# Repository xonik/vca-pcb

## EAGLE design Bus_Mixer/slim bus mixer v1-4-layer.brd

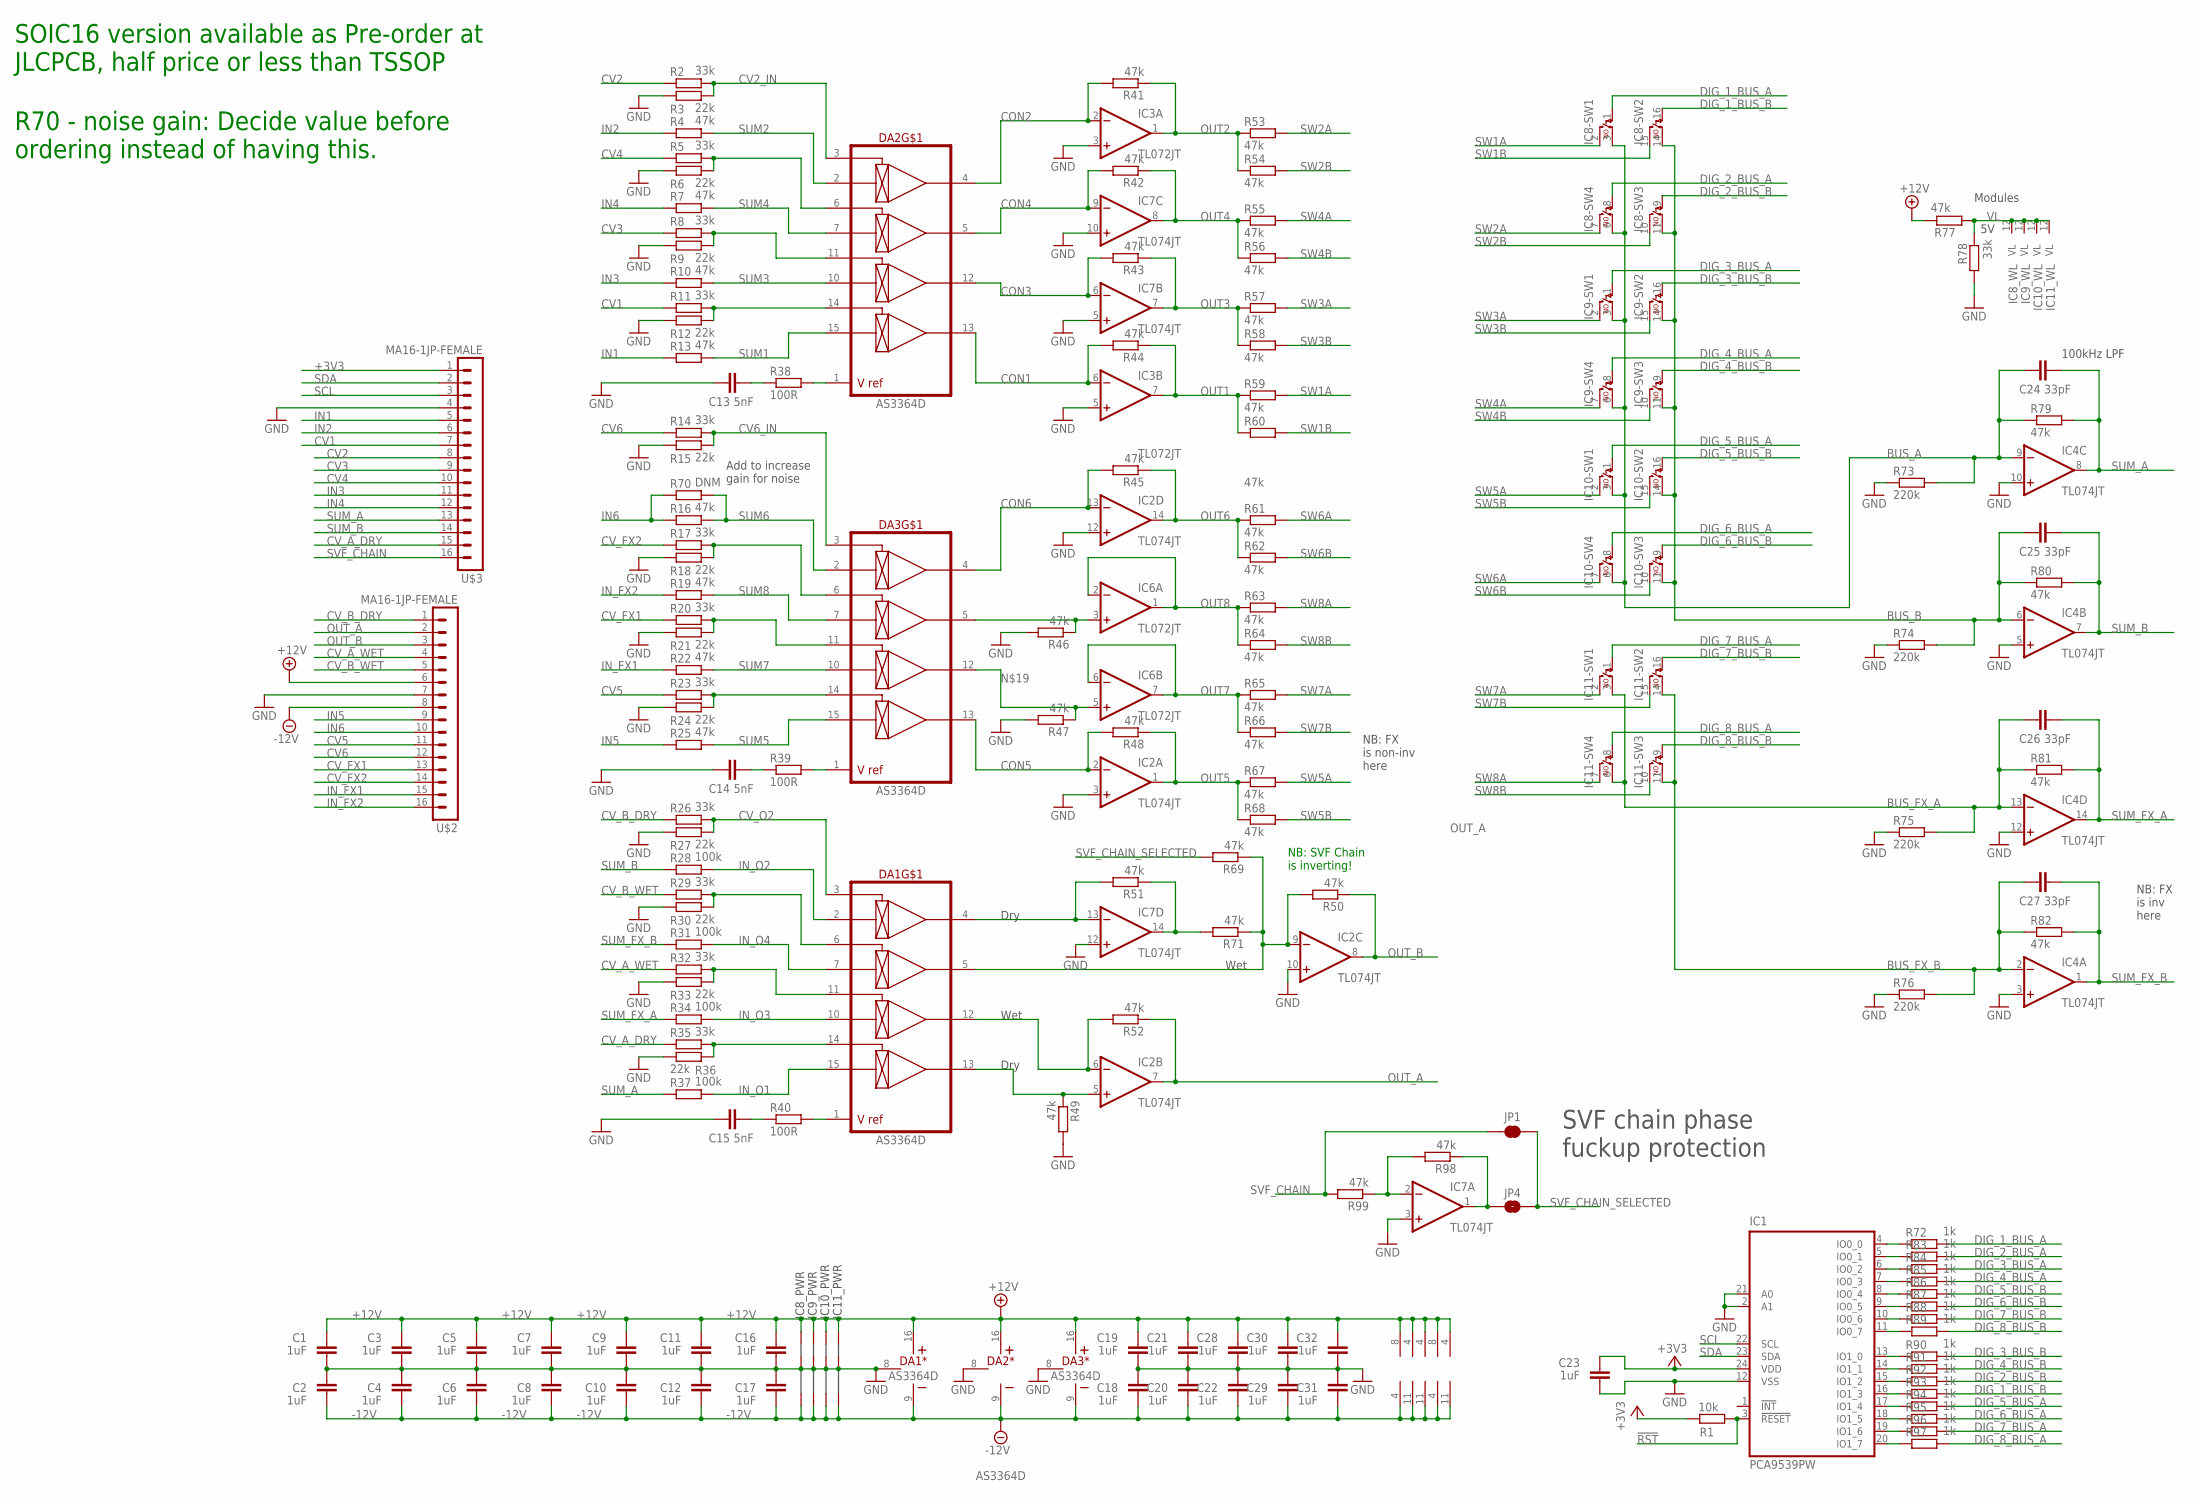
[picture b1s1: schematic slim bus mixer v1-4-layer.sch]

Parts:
C1, C2, C3, C4, C5, C6, C7, C8, C9, C10, C11, C12, C16, C17, C18, C19, C20, C21, C22, C23, C28, C29, C30, C31, C32: 1uF; C0402-J
C13, C14, C15: 5nF; C0402-J
C24, C25, C26, C27: 33pF; C0402-J
DA1, DA2, DA3: AS3364D; DIL16J
IC1: PCA9539PW; TSSOP24J
IC2, IC4, IC7: TL074JT; TSSOP14J
IC3, IC6: TL072JT; TSSOP8J
IC8, IC9, IC10, IC11: DG412-JS; SO-16
JP1: JUMPER-SMT_2_NC_TRACE_SILK-DNM; SMT-JUMPER_2_NC_TRACE_SILK
JP4: JUMPER-SMT_2_NO_SILK-DNM; SMT-JUMPER_2_NO_SILK
R1: 10k; R0402
R2, R5, R8, R11, R14, R17, R20, R23, R26, R29, R32, R35, R78: 33k; R0402
R3, R6, R9, R12, R15, R18, R21, R24, R27, R30, R33, R36: 22k; R0402
R4, R7, R10, R13, R16, R19, R22, R25, R41, R42, R43, R44, R45, R46, R47, R48, R49, R50, R51, R52, R53, R54, R55, R56, R57, R58, R59, R60, R61, R62, R63, R64, R65, R66, R67, R68, R69, R71, R77, R79, R80, R81, R82, R98, R99: 47k; R0402
R28, R31, R34, R37: 100k; R0402
R38, R39, R40: 100R; R0402
R70: DNM; R0805
R72, R83, R84, R85, R86, R87, R88, R89, R90, R91, R92, R93, R94, R95, R96, R97: 1k; R0402
R73, R74, R75, R76: 220k; R0603
U$2, U$3: MA16-1JP-FEMALE; SIP-PIN16-1J

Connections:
!RST: IC1.3 (!RESET), R1.2
+3V3: C23.2, IC1.24 (VDD), R1.1, U$3.1
+12V: C1.2, C3.2, C5.2, C7.2, C9.2, C11.2, C16.2, C19.2, C21.2, C28.2, C30.2, C32.2, DA1.16 (V+), DA2.16 (V+), DA3.16 (V+), IC2.4 (V+), IC3.8 (V+), IC4.4 (V+), IC6.8 (V+), IC7.4 (V+), IC8.13 (+15V), IC9.13 (+15V), IC10.13 (+15V), IC11.13 (+15V), R77.1, U$2.6
-12V: C2.1, C4.1, C6.1, C8.1, C10.1, C12.1, C17.1, C18.1, C20.1, C22.1, C29.1, C31.1, DA1.9 (V-), DA2.9 (V-), DA3.9 (V-), IC2.11 (V-), IC3.4 (V-), IC4.11 (V-), IC6.4 (V-), IC7.11 (V-), IC8.4 (-15V), IC9.4 (-15V), IC10.4 (-15V), IC11.4 (-15V), U$2.8
BUS_A: C24.1, IC4.9 (-IN), IC8.3 (S), IC8.6 (S), IC9.3 (S), IC9.6 (S), IC10.3 (S), IC10.6 (S), R73.2, R79.1
BUS_B: C25.1, IC4.6 (-IN), IC8.11 (S), IC8.14 (S), IC9.11 (S), IC9.14 (S), IC10.11 (S), IC10.14 (S), R74.2, R80.1
BUS_FX_A: C26.1, IC4.13 (-IN), IC11.3 (S), IC11.6 (S), R75.2, R81.1
BUS_FX_B: C27.1, IC4.2 (-IN), IC11.11 (S), IC11.14 (S), R76.2, R82.1
CON1: DA2.13 (OUT4), IC3.6 (-IN), R44.2
CON2: DA2.4 (OUT1), IC3.2 (-IN), R41.2
CON3: DA2.12 (OUT3), IC7.6 (-IN), R43.2
CON4: DA2.5 (OUT2), IC7.9 (-IN), R42.2
CON5: DA3.13 (OUT4), IC2.2 (-IN), R48.2
CON6: DA3.4 (OUT1), IC2.13 (-IN), R45.2
CON_O1: DA1.12 (OUT3), IC2.6 (-IN), R52.2
CV1: R11.1, U$3.7
CV2: R2.1, U$3.8
CV2_IN: DA2.3 (CV1), R2.2, R3.2
CV3: R8.1, U$3.9
CV4: R5.1, U$3.10
CV5: R23.1, U$2.11
CV6: R14.1, U$2.12
CV6_IN: DA3.3 (CV1), R14.2, R15.2
CV_A_DRY: R35.1, U$3.15
CV_A_WET: R32.1, U$2.4
CV_B_DRY: R26.1, U$2.1
CV_B_WET: R29.1, U$2.5
CV_FX1: R20.1, U$2.13
CV_FX2: R17.1, U$2.14
CV_O2: DA1.3 (CV1), R26.2, R27.2
DIG_1_BUS_A: IC8.1 (C), R72.2
DIG_1_BUS_B: IC8.16 (C), R93.2
DIG_2_BUS_A: IC8.8 (C), R83.2
DIG_2_BUS_B: IC8.9 (C), R92.2
DIG_3_BUS_A: IC9.1 (C), R84.2
DIG_3_BUS_B: IC9.16 (C), R90.2
DIG_4_BUS_A: IC9.8 (C), R85.2
DIG_4_BUS_B: IC9.9 (C), R91.2
DIG_5_BUS_A: IC10.1 (C), R94.2
DIG_5_BUS_B: IC10.16 (C), R86.2
DIG_6_BUS_A: IC10.8 (C), R95.2
DIG_6_BUS_B: IC10.9 (C), R87.2
DIG_7_BUS_A: IC11.1 (C), R96.2
DIG_7_BUS_B: IC11.16 (C), R88.2
DIG_8_BUS_A: IC11.8 (C), R97.2
DIG_8_BUS_B: IC11.9 (C), R89.2
GND: C1.1, C2.2, C3.1, C4.2, C5.1, C6.2, C7.1, C8.2, C9.1, C10.2, C11.1, C12.2, C13.1, C14.1, C15.1, C16.1, C17.2, C18.2, C19.1, C20.2, C21.1, C22.2, C23.1, C28.1, C29.2, C30.1, C31.2, C32.1, DA1.8 (GND), DA2.8 (GND), DA3.8 (GND), IC1.2 (A1), IC1.12 (VSS), IC1.21 (A0), IC2.3 (+IN), IC2.10 (+IN), IC2.12 (+IN), IC3.3 (+IN), IC3.5 (+IN), IC4.3 (+IN), IC4.5 (+IN), IC4.10 (+IN), IC4.12 (+IN), IC7.3 (+IN), IC7.5 (+IN), IC7.10 (+IN), IC7.12 (+IN), IC8.5 (AGND), IC9.5 (AGND), IC10.5 (AGND), IC11.5 (AGND), R3.1, R6.1, R9.1, R12.1, R15.1, R18.1, R21.1, R24.1, R27.1, R30.1, R33.1, R36.1, R46.2, R47.2, R49.2, R73.1, R74.1, R75.1, R76.1, R78.2, U$2.7, U$3.4
IN1: R13.1, U$3.5
IN2: R4.1, U$3.6
IN3: R10.1, U$3.11
IN4: R7.1, U$3.12
IN5: R25.1, U$2.9
IN6: R16.1, R70.1, U$2.10
IN_FX1: R22.1, U$2.15
IN_FX2: R19.1, U$2.16
IN_O1: DA1.15 (IN4), R37.2
IN_O2: DA1.2 (IN1), R28.2
IN_O3: DA1.10 (IN3), R34.2
IN_O4: DA1.7 (IN2), R31.2
unnamed: DA3.1 (VREF), R39.2
unnamed: DA2.1 (VREF), R38.2
unnamed: DA3.6 (CV2), R17.2, R18.2
unnamed: DA3.5 (OUT2), IC6.3 (+IN), R46.1
unnamed: DA3.11 (CV3), R20.2, R21.2
unnamed: DA1.5 (OUT2), IC2.9 (-IN), R50.2, R69.1, R71.1
unnamed: DA3.14 (CV4), R23.2, R24.2
unnamed: C14.2, R39.1
unnamed: DA1.1 (VREF), R40.2
unnamed: DA2.6 (CV2), R5.2, R6.2
unnamed: DA1.6 (CV2), R29.2, R30.2
unnamed: DA2.11 (CV3), R8.2, R9.2
unnamed: DA1.11 (CV3), R32.2, R33.2
unnamed: C13.2, R38.1
unnamed: DA1.14 (CV4), R35.2, R36.2
unnamed: C15.2, R40.1
unnamed: DA1.4 (OUT1), IC7.13 (-IN), R51.2
unnamed: DA1.13 (OUT4), IC2.5 (+IN), R49.1
unnamed: DA3.12 (OUT3), IC6.5 (+IN), R47.1
unnamed: IC7.14 (OUT), R51.1, R71.2
unnamed: DA2.14 (CV4), R11.2, R12.2
unnamed: IC7.1 (OUT), JP4.1, R98.1
unnamed: IC1.4 (IO0_0), R72.1
unnamed: IC1.5 (IO0_1), R83.1
unnamed: IC1.6 (IO0_2), R84.1
unnamed: IC1.7 (IO0_3), R85.1
unnamed: IC1.8 (IO0_4), R86.1
unnamed: IC1.9 (IO0_5), R87.1
unnamed: IC1.10 (IO0_6), R88.1
unnamed: IC1.11 (IO0_7), R89.1
unnamed: IC1.13 (IO1_0), R90.1
unnamed: IC1.14 (IO1_1), R91.1
unnamed: IC1.15 (IO1_2), R92.1
unnamed: IC1.16 (IO1_3), R93.1
unnamed: IC1.17 (IO1_4), R94.1
unnamed: IC1.18 (IO1_5), R95.1
unnamed: IC1.19 (IO1_6), R96.1
unnamed: IC1.20 (IO1_7), R97.1
unnamed: IC7.2 (-IN), R98.2, R99.1
OUT1: IC3.7 (OUT), R44.1, R59.1, R60.1
OUT2: IC3.1 (OUT), R41.1, R53.1, R54.1
OUT3: IC7.7 (OUT), R43.1, R57.1, R58.1
OUT4: IC7.8 (OUT), R42.1, R55.1, R56.1
OUT5: IC2.1 (OUT), R48.1, R67.1, R68.1
OUT6: IC2.14 (OUT), R45.1, R61.1, R62.1
OUT7: IC6.6 (-IN), IC6.7 (OUT), R65.1, R66.1
OUT8: IC6.1 (OUT), IC6.2 (-IN), R63.1, R64.1
OUT_A: IC2.7 (OUT), R52.1, U$2.2
OUT_B: IC2.8 (OUT), R50.1, U$2.3
SCL: IC1.22 (SCL), U$3.3
SDA: IC1.23 (SDA), U$3.2
SUM1: DA2.15 (IN4), R13.2
SUM2: DA2.2 (IN1), R4.2
SUM3: DA2.10 (IN3), R10.2
SUM4: DA2.7 (IN2), R7.2
SUM5: DA3.15 (IN4), R25.2
SUM6: DA3.2 (IN1), R16.2, R70.2
SUM7: DA3.10 (IN3), R22.2
SUM8: DA3.7 (IN2), R19.2
SUM_A: C24.2, IC4.8 (OUT), R37.1, R79.2, U$3.13
SUM_B: C25.2, IC4.7 (OUT), R28.1, R80.2, U$3.14
SUM_FX_A: C26.2, IC4.14 (OUT), R34.1, R81.2
SUM_FX_B: C27.2, IC4.1 (OUT), R31.1, R82.2
SVF_CHAIN: JP1.1, R99.2, U$3.16
SVF_CHAIN_SELECTED: JP1.2, JP4.2, R69.2
SW1A: IC8.2 (D), R59.2
SW1B: IC8.15 (D), R60.2
SW2A: IC8.7 (D), R53.2
SW2B: IC8.10 (D), R54.2
SW3A: IC9.2 (D), R57.2
SW3B: IC9.15 (D), R58.2
SW4A: IC9.7 (D), R55.2
SW4B: IC9.10 (D), R56.2
SW5A: IC10.2 (D), R67.2
SW5B: IC10.15 (D), R68.2
SW6A: IC10.7 (D), R61.2
SW6B: IC10.10 (D), R62.2
SW7A: IC11.2 (D), R65.2
SW7B: IC11.15 (D), R66.2
SW8A: IC11.7 (D), R63.2
SW8B: IC11.10 (D), R64.2
VL: IC8.12 (VL), IC9.12 (VL), IC10.12 (VL), IC11.12 (VL), R77.2, R78.1

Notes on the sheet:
SVF chain phase fuckup protection
Modules
100kHz LPF
Wet
Dry
NB: FX is non-inv here
NB: FX is inv here
R70 - noise gain: Decide value before ordering instead of having this.
NB: SVF Chain is inverting!
Add to increase gain for noise
SOIC16 version available as Pre-order at JLCPCB, half price or less than TSSOP

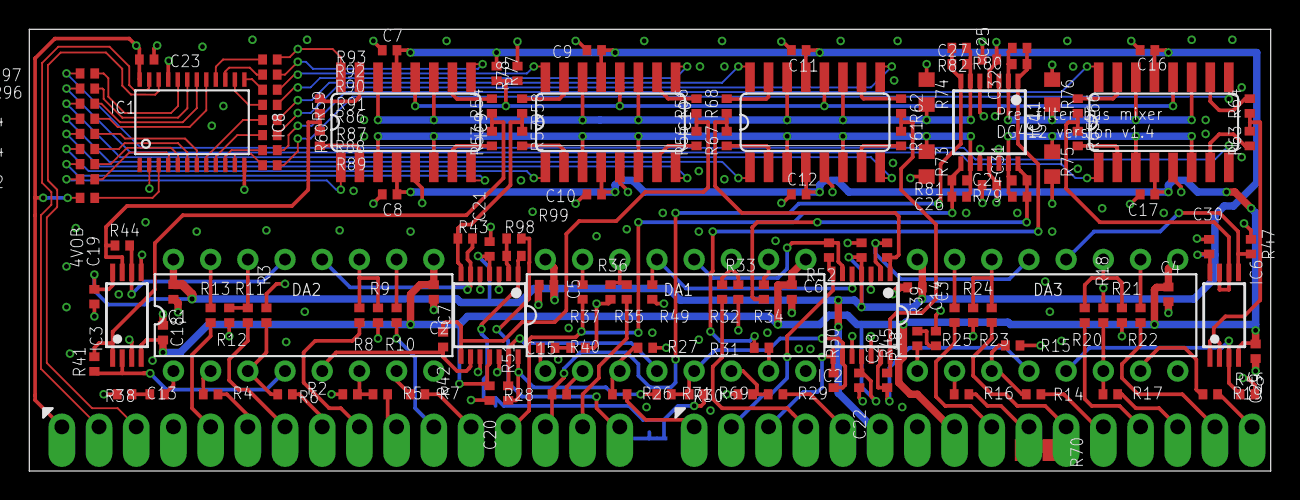
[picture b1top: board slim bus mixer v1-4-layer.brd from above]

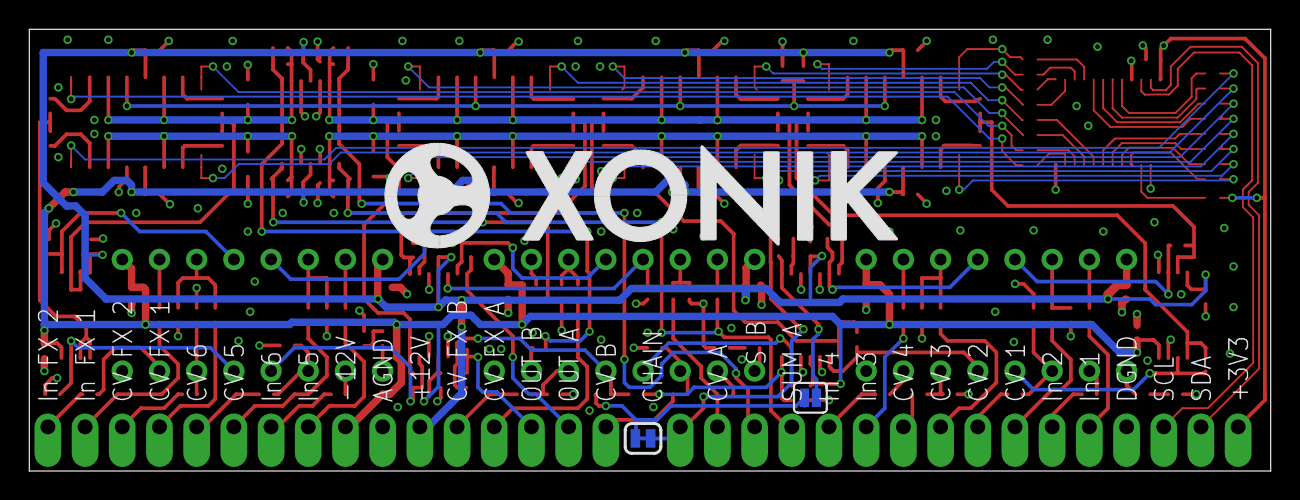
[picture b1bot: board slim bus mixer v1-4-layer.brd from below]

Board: 4 copper layers, 84.8 x 30.2 mm, 149 parts (3 on the bottom side), 141 nets.

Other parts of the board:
U$1: XONIK_LOGO_35

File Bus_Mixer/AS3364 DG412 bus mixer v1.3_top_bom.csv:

Comment,Designator,Footprint,LCSC Part #
1uF,C1 C2 C3 C4 C5 C6 C7 C8 C9 C10 C11 C12 C16 C17,C0402-J,
1uF,C18 C19 C20 C21 C22 C23,C0402,
5nF,C13 C14 C15,C0402-J,
10k,R1,R0402,
22k,R3 R6 R9 R12 R15 R18 R21 R24 R27 R30 R33 R36,R0402,
33k,R2 R5 R8 R11 R14 R17 R20 R23 R26 R29 R32 R35 R78,R0402,
33pF,C24 C25 C26 C27,C0402-J,
47k,R4 R7 R10 R13 R16 R19 R22 R25 R28 R31 R34 R37 R41 R42 R43 R44 R45 R46 R47 R48 R49 R50 R51 R52 R53 R54 R55 R56 R57 R58 R59 R60 R61 R62 R63 R64 R65 R66 R67 R68 R69 R77 R79 R80 R81 R82,R0402,
100R,R38 R39 R40,R0402,
220k,R73 R74 R75 R76,R0603,
AS3364D,DA1 DA2 DA3,DIL16J,
DG412-J,IC8 IC9 IC10 IC11,DIL16J,
DNM,R70,R0805,
MA16-1JP-FEMALE,U$2 U$3,SIP-PIN16-1J,
PCA9539PW,IC1,TSSOP24J,
TL072JT,IC3 IC5 IC6,TSSOP8J,
TL074JT,IC2 IC4,TSSOP14J,

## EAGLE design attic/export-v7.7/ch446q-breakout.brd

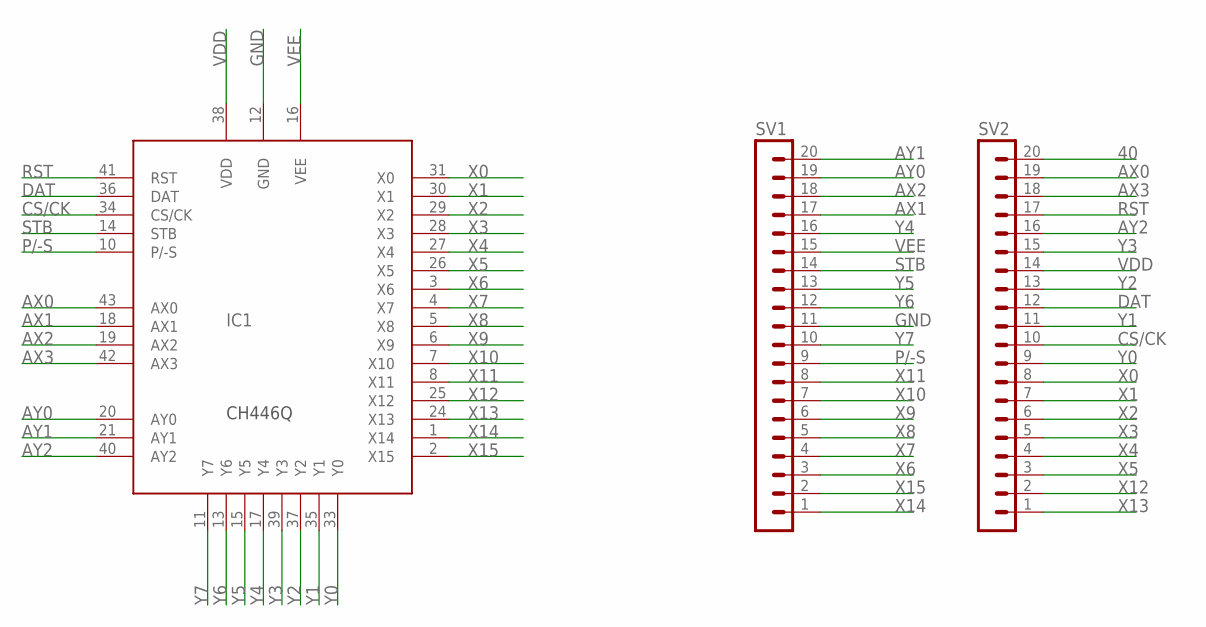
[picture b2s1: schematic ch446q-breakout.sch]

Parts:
IC1: CH446Q; LQFP-44-J
SV1, SV2: MA20-1JC; MA20-1J

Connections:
40: SV2.20
AX0: IC1.43 (AX0), SV2.19
AX1: IC1.18 (AX1), SV1.17
AX2: IC1.19 (AX2), SV1.18
AX3: IC1.42 (AX3), SV2.18
AY0: IC1.20 (AY0), SV1.19
AY1: IC1.21 (AY1), SV1.20
AY2: IC1.40 (AY2), SV2.16
CS/CK: IC1.34 (CS/CK), SV2.10
DAT: IC1.36 (DAT), SV2.12
GND: IC1.12 (GND), SV1.11
P/-S: IC1.10 (P/-S), SV1.9
RST: IC1.41 (RST), SV2.17
STB: IC1.14 (STB), SV1.14
VDD: IC1.38 (VDD), SV2.14
VEE: IC1.16 (VEE), SV1.15
X0: IC1.31 (X0), SV2.8
X1: IC1.30 (X1), SV2.7
X2: IC1.29 (X2), SV2.6
X3: IC1.28 (X3), SV2.5
X4: IC1.27 (X4), SV2.4
X5: IC1.26 (X5), SV2.3
X6: IC1.3 (X6), SV1.3
X7: IC1.4 (X7), SV1.4
X8: IC1.5 (X8), SV1.5
X9: IC1.6 (X9), SV1.6
X10: IC1.7 (X10), SV1.7
X11: IC1.8 (X11), SV1.8
X12: IC1.25 (X12), SV2.2
X13: IC1.24 (X13), SV2.1
X14: IC1.1 (X14), SV1.1
X15: IC1.2 (X15), SV1.2
Y0: IC1.33 (Y0), SV2.9
Y1: IC1.35 (Y1), SV2.11
Y2: IC1.37 (Y2), SV2.13
Y3: IC1.39 (Y3), SV2.15
Y4: IC1.17 (Y4), SV1.16
Y5: IC1.15 (Y5), SV1.13
Y6: IC1.13 (Y6), SV1.12
Y7: IC1.11 (Y7), SV1.10

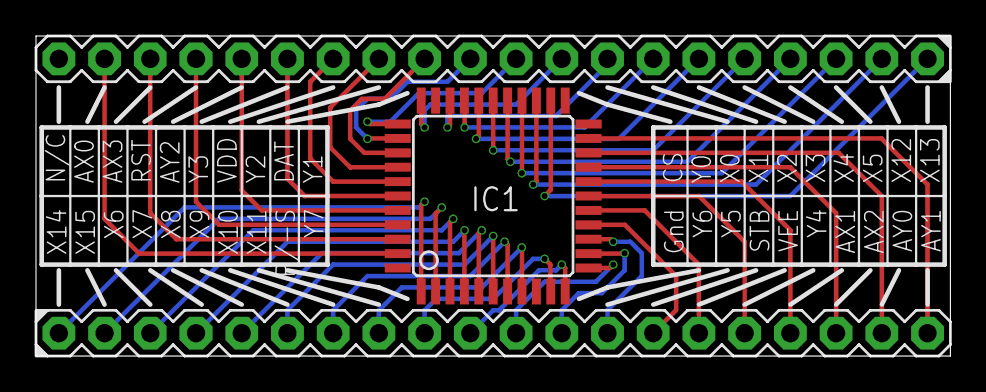
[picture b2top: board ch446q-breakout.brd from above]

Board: 2 copper layers, 50.8 x 17.8 mm, 3 parts (0 on the bottom side), 39 nets.

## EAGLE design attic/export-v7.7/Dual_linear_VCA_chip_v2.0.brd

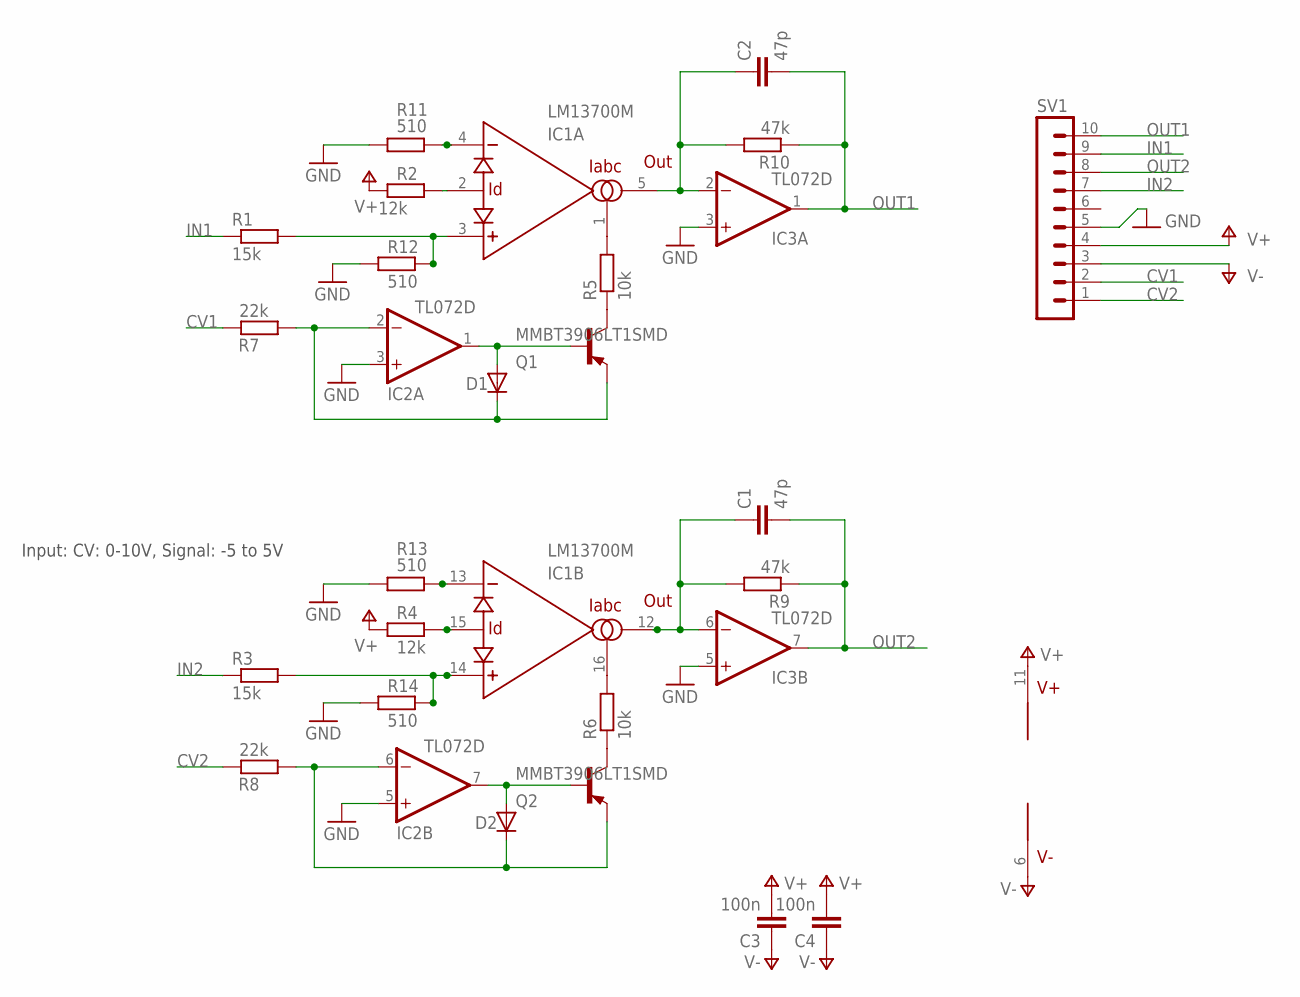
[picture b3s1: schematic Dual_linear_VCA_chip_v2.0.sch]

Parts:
C1, C2: 47p; C0805
C3, C4: 100n; C0805
D1, D2: DIODE-SOD80C; SOD80C
IC1: LM13700M; SO16
IC2, IC3: TL072D; SO08
Q1, Q2: MMBT3906LT1SMD; SOT23-BEC
R1, R3: 15k; R0805
R2, R4: 12k; R0805
R5, R6: 10k; R0805
R7, R8: 22k; R0805
R9, R10: 47k; R0805
R11, R12, R13, R14: 510; R0805
SV1: MA10-1

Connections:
CV1: R7.2, SV1.2
CV2: R8.2, SV1.1
GND: IC2.3 (+IN), IC2.5 (+IN), IC3.3 (+IN), IC3.5 (+IN), R11.1, R12.1, R13.1, R14.1, SV1.5
IN1: R1.1, SV1.9
IN2: R3.1, SV1.7
unnamed: Q1.C, R5.1
unnamed: Q2.C, R6.1
unnamed: D1.C, IC2.2 (-IN), Q1.E, R7.1
unnamed: IC1.1 (IABC), R5.2
unnamed: IC1.2 (ID), R2.2
unnamed: D2.A, IC2.7 (OUT), Q2.B
unnamed: C2.1, IC1.5 (OUT), IC3.2 (-IN), R10.2
unnamed: D1.A, IC2.1 (OUT), Q1.B
unnamed: D2.C, IC2.6 (-IN), Q2.E, R8.1
unnamed: IC1.16 (IABC), R6.2
unnamed: IC1.15 (ID), R4.2
unnamed: C1.1, IC1.12 (OUT), IC3.6 (-IN), R9.2
OUT1: C2.2, IC3.1 (OUT), R10.1, SV1.10
OUT2: C1.2, IC3.7 (OUT), R9.1, SV1.8
TRIM1+: IC1.3 (+IN), R1.2, R12.2
TRIM1-: IC1.4 (-IN), R11.2
TRIM2+: IC1.14 (+IN), R3.2, R14.2
TRIM2-: IC1.13 (-IN), R13.2
V+: C3.2, C4.2, IC1.11 (V+), IC2.8 (V+), IC3.8 (V+), R2.1, R4.1, SV1.4
V-: C3.1, C4.1, IC1.6 (V-), IC2.4 (V-), IC3.4 (V-), SV1.3

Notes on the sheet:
Input: CV: 0-10V, Signal: -5 to 5V

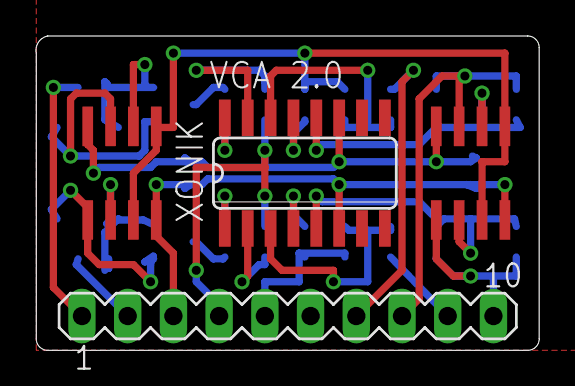
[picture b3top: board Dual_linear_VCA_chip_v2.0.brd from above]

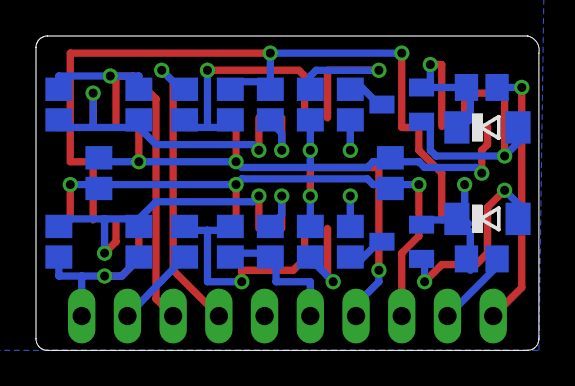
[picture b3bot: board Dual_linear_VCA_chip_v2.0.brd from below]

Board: 2 copper layers, 28.0 x 17.5 mm, 26 parts (22 on the bottom side), 25 nets.

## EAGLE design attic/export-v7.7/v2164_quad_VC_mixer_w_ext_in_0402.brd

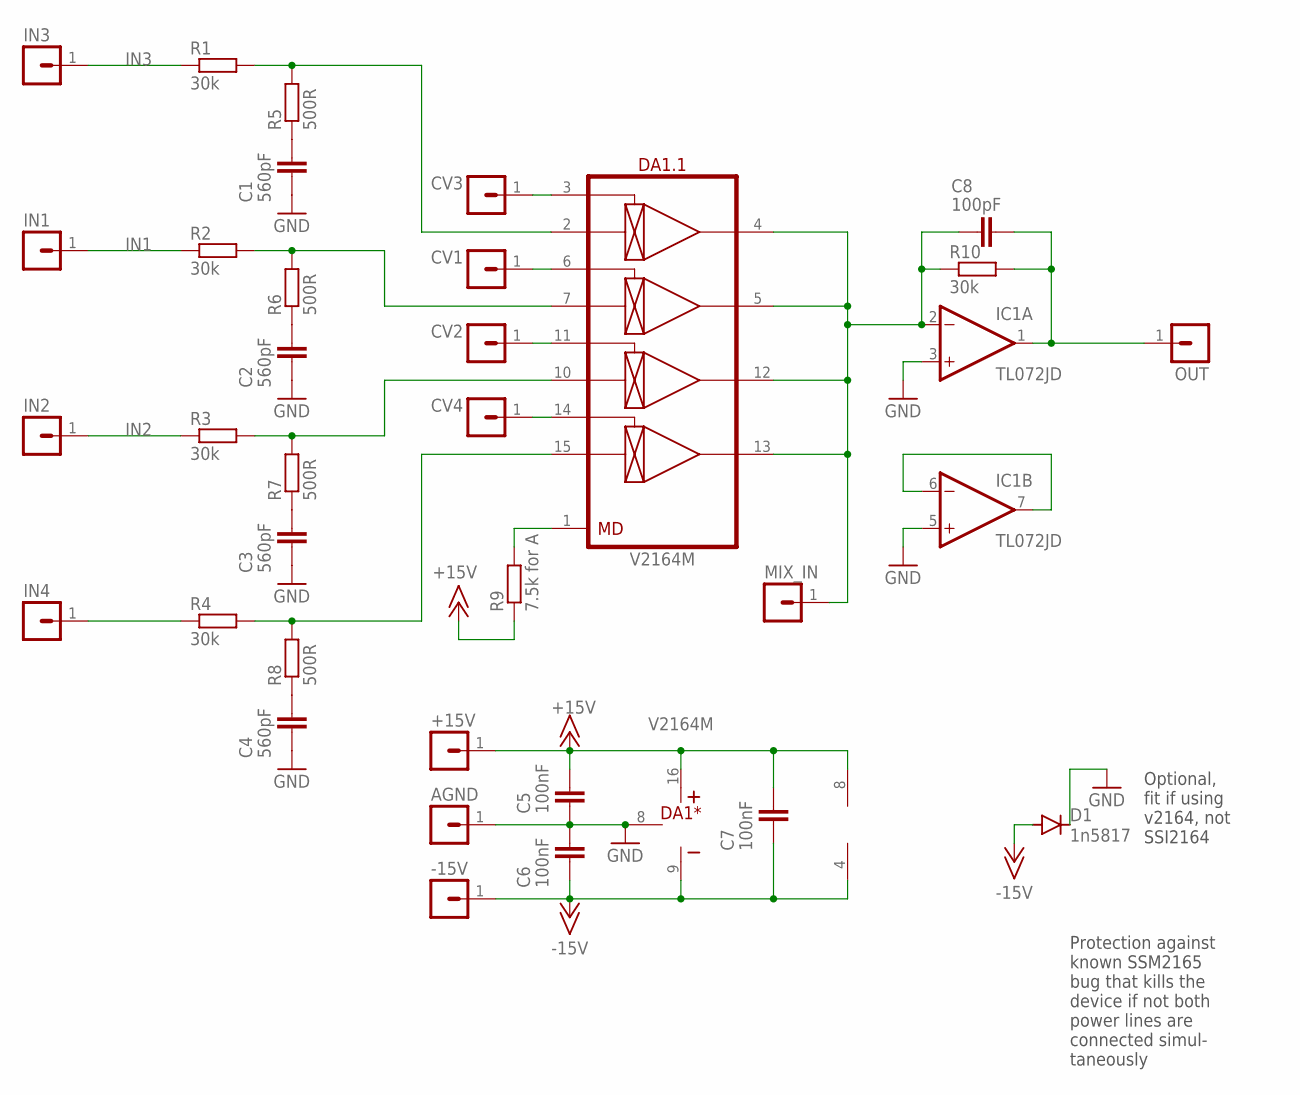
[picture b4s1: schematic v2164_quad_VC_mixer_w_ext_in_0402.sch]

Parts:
+15V: MA01-1JN; MA01N-1J
-15V: MA01-1JN; MA01N-1J
AGND: MA01-1JN; MA01N-1J
C1, C2, C3, C4: 560pF; C0603
C5, C6, C7: 100nF; C0402
C8: 100pF; C0402
CV1, CV2, CV3, CV4: MA01-1JN; MA01N-1J
D1: 1n5817; SOD323-R
DA1: V2164M; SO-16
IC1: TL072JD; SO08J
IN1, IN2, IN3, IN4: MA01-1JN; MA01N-1J
MIX_IN: MA01-1JN; MA01N-1J
OUT: MA01-1JN; MA01N-1J
R1, R2, R3, R4, R10: 30k; R0402
R5, R6, R7, R8: 500R; R0402
R9: 7.5k for A; R0402

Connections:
+15V: +15V.1, C5.2, C7.2, DA1.16 (V+), IC1.8 (V+), R9.1
-15V: -15V.1, C6.1, C7.1, D1.A, DA1.9 (V-), IC1.4 (V-)
CV1: CV1.1, DA1.6 (CV2)
CV2: CV2.1, DA1.11 (CV3)
CV4: CV4.1, DA1.14 (CV4)
CV5: CV3.1, DA1.3 (CV1)
GND: AGND.1, C1.1, C2.1, C3.1, C4.1, C5.1, C6.2, D1.C, DA1.8 (GND), IC1.3 (+IN), IC1.5 (+IN)
IN1: IN1.1, R2.1
IN2: IN2.1, R3.1
IN3: IN3.1, R1.1
IN4: IN4.1, R4.1
unnamed: IC1.6 (-IN), IC1.7 (OUT)
unnamed: DA1.1 (MD), R9.2
unnamed: C8.1, DA1.4 (OUT1), DA1.5 (OUT2), DA1.12 (OUT3), DA1.13 (OUT4), IC1.2 (-IN), MIX_IN.1, R10.1
unnamed: C1.2, R5.1
unnamed: C2.2, R6.1
unnamed: C3.2, R7.1
unnamed: C4.2, R8.1
unnamed: DA1.2 (IN1), R1.2, R5.2
unnamed: DA1.7 (IN2), R2.2, R6.2
unnamed: DA1.10 (IN3), R3.2, R7.2
unnamed: DA1.15 (IN4), R4.2, R8.2
OUT: C8.2, IC1.1 (OUT), OUT.1, R10.2

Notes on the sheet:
Optional, fit if using v2164, not SSI2164
Protection against known SSM2165 bug that kills the device if not both power lines are connected simul- taneously

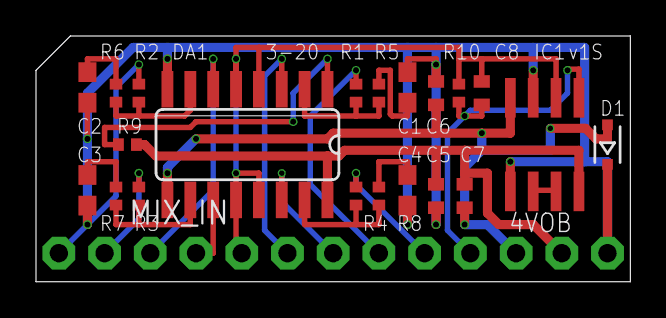
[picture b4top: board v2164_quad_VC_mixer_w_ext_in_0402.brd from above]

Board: 2 copper layers, 33.0 x 13.7 mm, 35 parts (1 on the bottom side), 23 nets.

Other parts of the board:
U$1: XONIK_LOGO_20

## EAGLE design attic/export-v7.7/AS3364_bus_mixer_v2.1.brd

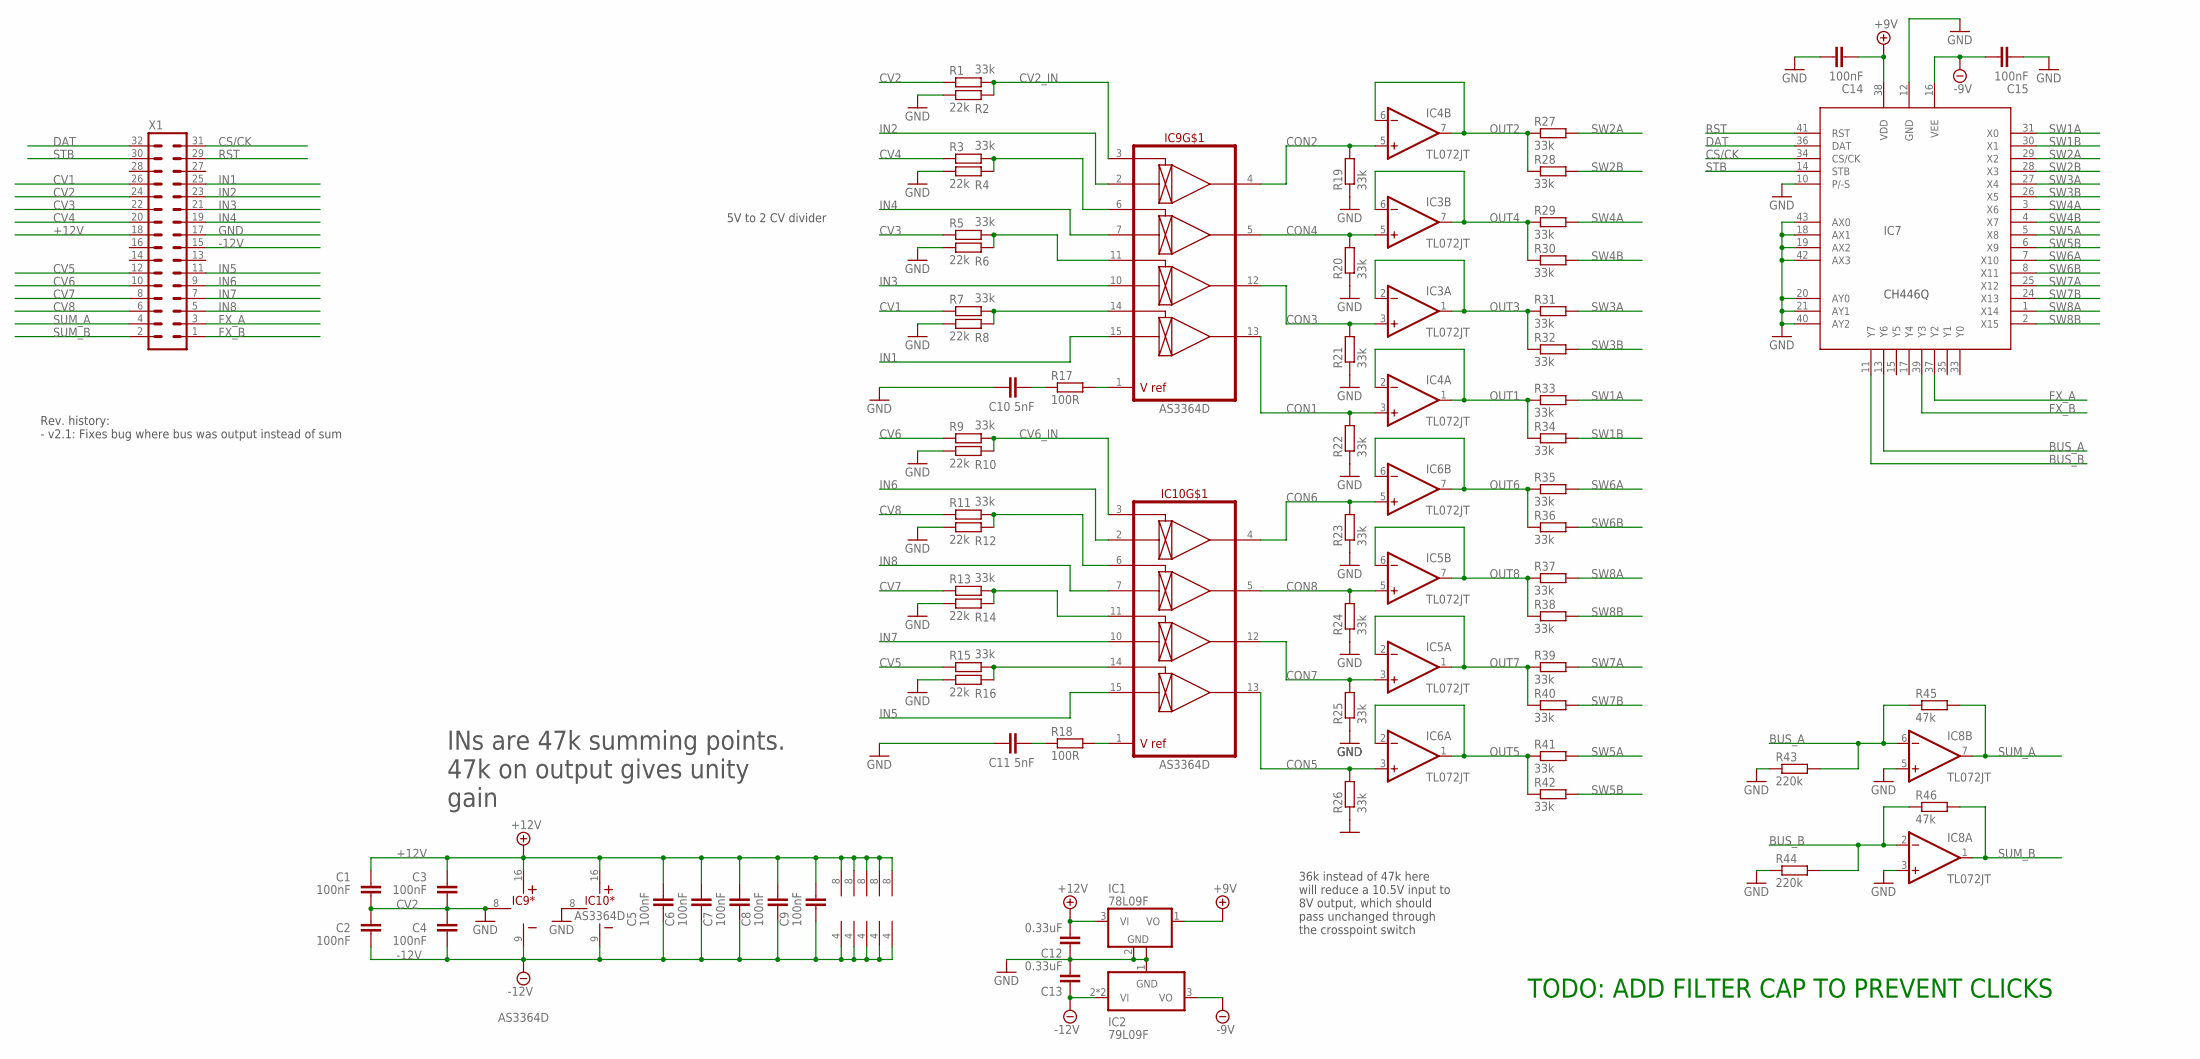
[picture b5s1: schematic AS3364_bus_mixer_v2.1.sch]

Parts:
C1, C2, C3, C4, C5, C6, C7, C8, C9, C14, C15: 100nF; C0402
C10, C11: 5nF; C0402
C12, C13: 0.33uF; C0603
IC1: 78L09F; SOT89
IC2: 79L09F; SOT89
IC3, IC4, IC5, IC6, IC8: TL072JT; TSSOP8J
IC7: CH446Q; LQFP-44-J
IC9, IC10: AS3364D; DIL16J
R1, R3, R5, R7, R9, R11, R13, R15, R19, R20, R21, R22, R23, R24, R25, R26, R27, R28, R29, R30, R31, R32, R33, R34, R35, R36, R37, R38, R39, R40, R41, R42: 33k; R0402
R2, R4, R6, R8, R10, R12, R14, R16: 22k; R0402
R17, R18: 100R; R0402
R43, R44: 220k; R0402
R45, R46: 47k; R0402
X1: MA16-2WJ

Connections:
+9V: C14.1, IC1.1 (VO), IC7.38 (VDD)
+12V: C1.2, C3.2, C5.2, C6.2, C7.2, C8.2, C9.2, C12.2, IC1.3 (VI), IC3.8 (V+), IC4.8 (V+), IC5.8 (V+), IC6.8 (V+), IC8.8 (V+), IC9.16 (V+), IC10.16 (V+), X1.18
-9V: C15.2, IC2.3 (VO), IC7.16 (VEE)
-12V: C2.1, C4.1, C5.1, C6.1, C7.1, C8.1, C9.1, C13.1, IC2.2 (VI), IC2.2@1 (VI), IC3.4 (V-), IC4.4 (V-), IC5.4 (V-), IC6.4 (V-), IC8.4 (V-), IC9.9 (V-), IC10.9 (V-), X1.15
BUS_A: IC7.13 (Y6), IC8.6 (-IN), R43.2, R45.1
BUS_B: IC7.11 (Y7), IC8.2 (-IN), R44.2, R46.1
CON1: IC4.3 (+IN), IC9.13 (OUT4), R22.2
CON2: IC4.5 (+IN), IC9.4 (OUT1), R19.2
CON3: IC3.3 (+IN), IC9.12 (OUT3), R21.2
CON4: IC3.5 (+IN), IC9.5 (OUT2), R20.2
CON5: IC6.3 (+IN), IC10.13 (OUT4), R26.2
CON6: IC6.5 (+IN), IC10.4 (OUT1), R23.2
CON7: IC5.3 (+IN), IC10.12 (OUT3), R25.2
CON8: IC5.5 (+IN), IC10.5 (OUT2), R24.2
CS/CK: IC7.34 (CS/CK), X1.31
CV1: R7.1, X1.26
CV2: R1.1, X1.24
CV2_IN: IC9.3 (CV1), R1.2, R2.2
CV3: R5.1, X1.22
CV4: R3.1, X1.20
CV5: R15.1, X1.12
CV6: R9.1, X1.10
CV6_IN: IC10.3 (CV1), R9.2, R10.2
CV7: R13.1, X1.8
CV8: R11.1, X1.6
DAT: IC7.36 (DAT), X1.32
FX_A: IC7.37 (Y2), X1.3
FX_B: IC7.39 (Y3), X1.1
GND: C1.1, C2.2, C3.1, C4.2, C10.1, C11.1, C12.1, C13.2, C14.2, C15.1, IC1.2 (GND), IC1.2@1 (GND), IC2.1 (GND), IC7.10 (P/-S), IC7.12 (GND), IC7.18 (AX1), IC7.19 (AX2), IC7.20 (AY0), IC7.21 (AY1), IC7.40 (AY2), IC7.42 (AX3), IC7.43 (AX0), IC8.3 (+IN), IC8.5 (+IN), IC9.8 (GND), IC10.8 (GND), R2.1, R4.1, R6.1, R8.1, R10.1, R12.1, R14.1, R16.1, R19.1, R20.1, R21.1, R22.1, R23.1, R24.1, R25.1, R26.1, R43.1, R44.1, X1.17
IN1: IC9.15 (IN4), X1.25
IN2: IC9.2 (IN1), X1.23
IN3: IC9.10 (IN3), X1.21
IN4: IC9.7 (IN2), X1.19
IN5: IC10.15 (IN4), X1.11
IN6: IC10.2 (IN1), X1.9
IN7: IC10.10 (IN3), X1.7
IN8: IC10.7 (IN2), X1.5
unnamed: IC10.1 (VREF), R18.2
unnamed: IC9.1 (VREF), R17.2
unnamed: IC10.6 (CV2), R11.2, R12.2
unnamed: IC10.11 (CV3), R13.2, R14.2
unnamed: IC10.14 (CV4), R15.2, R16.2
unnamed: C11.2, R18.1
unnamed: IC9.6 (CV2), R3.2, R4.2
unnamed: IC9.11 (CV3), R5.2, R6.2
unnamed: C10.2, R17.1
unnamed: IC9.14 (CV4), R7.2, R8.2
OUT1: IC4.1 (OUT), IC4.2 (-IN), R33.1, R34.1
OUT2: IC4.6 (-IN), IC4.7 (OUT), R27.1, R28.1
OUT3: IC3.1 (OUT), IC3.2 (-IN), R31.1, R32.1
OUT4: IC3.6 (-IN), IC3.7 (OUT), R29.1, R30.1
OUT5: IC6.1 (OUT), IC6.2 (-IN), R41.1, R42.1
OUT6: IC6.6 (-IN), IC6.7 (OUT), R35.1, R36.1
OUT7: IC5.1 (OUT), IC5.2 (-IN), R39.1, R40.1
OUT8: IC5.6 (-IN), IC5.7 (OUT), R37.1, R38.1
RST: IC7.41 (RST), X1.29
STB: IC7.14 (STB), X1.30
SUM_A: IC8.7 (OUT), R45.2, X1.4
SUM_B: IC8.1 (OUT), R46.2, X1.2
SW1A: IC7.31 (X0), R33.2
SW1B: IC7.30 (X1), R34.2
SW2A: IC7.29 (X2), R27.2
SW2B: IC7.28 (X3), R28.2
SW3A: IC7.27 (X4), R31.2
SW3B: IC7.26 (X5), R32.2
SW4A: IC7.3 (X6), R29.2
SW4B: IC7.4 (X7), R30.2
SW5A: IC7.5 (X8), R41.2
SW5B: IC7.6 (X9), R42.2
SW6A: IC7.7 (X10), R35.2
SW6B: IC7.8 (X11), R36.2
SW7A: IC7.25 (X12), R39.2
SW7B: IC7.24 (X13), R40.2
SW8A: IC7.1 (X14), R37.2
SW8B: IC7.2 (X15), R38.2

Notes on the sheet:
INs are 47k summing points. 47k on output gives unity gain
5V to 2 CV divider
36k instead of 47k here will reduce a 10.5V input to 8V output, which should pass unchanged through the crosspoint switch
Rev. history: - v2.1: Fixes bug where bus was output instead of sum
TODO: ADD FILTER CAP TO PREVENT CLICKS

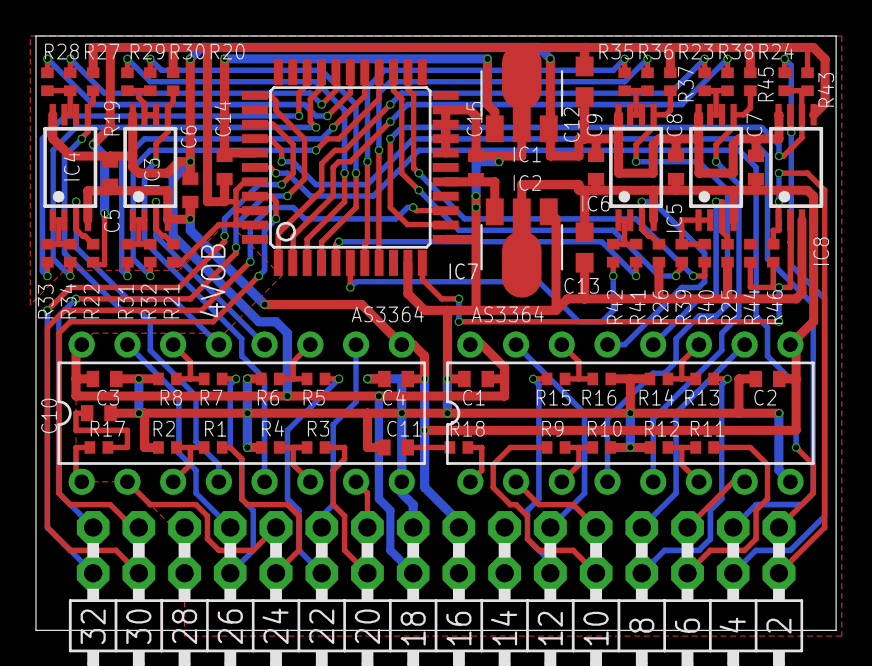
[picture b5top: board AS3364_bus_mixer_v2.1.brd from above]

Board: 2 copper layers, 44.5 x 33.0 mm, 73 parts (1 on the bottom side), 75 nets.

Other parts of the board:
U$1: XONIK_LOGO_28

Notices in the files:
parts and their libraries:
SparkFun-Jumpers: Licensing: Creative Commons ShareAlike 4.0 International - https://creativecommons.org/licenses/by-sa/4.0
